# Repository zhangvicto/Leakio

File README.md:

## Inspiration
Over one-fourth of Canadians during their lifetimes will have to deal with water damage in their homes. This is an issue that causes many Canadians overwhelming stress from the sheer economical and residential implications. 

As an effort to assist and solve these very core issues, we have designed a solution that will allow for future leaks to be avoidable. Our prototype system made, composed of software and hardware will ensure house leaks are a thing of the past!

## What is our planned solution?

To prevent leaks, we have designed a system of components that when functioning together, would allow the user to monitor the status of their plumbing systems. 

Our system is comprised of:
> 
Two types of leak detection hardware
- Acoustic leak detectors: monitors abnormal sounds of pipes.
- Water detection probes: monitors the presence of water in unwanted areas.

Our hardware components will have the ability to send data to a local network, to then be stored in the cloud.

> Software components
- Secure cloud to store vital information regarding pipe leakages.
- Future planned app/website with the ability to receive such information

## Business Aspect of Leakio
Standalone, this solution is profitable through the aspect of selling the specific hardware to consumers. Although for insurance companies, this is a vital solution that has the potential to save millions of dollars.

It is far more economical to prevent a leak, rather than fix it when it already happens. The time of paying the average cost of $10,900 US dollars to fix water damage or a freezing claim is now avoidable!

In addition to saved funds, our planned system will be able to send information to insurance companies for specific data purposes such as which houses or areas have the most leaks, or individual risk assessment. This would allow insurance companies to more appropriately create better rates for the consumer, for the benefit of both consumer and insurance company.

## Software
### Front End:
This includes our app design in Figma, which was crafted using knowledge on proper design and ratios. Specifically, we wanted to create an app design that looked simple but had all the complex features that would seem professional. This is something we are proud of, as we feel this component was successful.

### Back End:
- PHP: website to retrieve data from Cloud SQL
- MySQL: access database through Raspberry Pi
- Python: using mysql connector to upload data to Cloud SQL
- Cloud SQL: Google MySQL database

## Hardware
### Electrical
- A custom PCB is designed from scratch using EAGLE
- Consists of USBC charging port, lithium battery charging circuit, ESP32, Water sensor connector, microphone connector
- The water sensor and microphone are extended from the PCB which is why they need a connector

### Custom Water Sensor
Two wires and an analog input.

### 3D-model
- Hub contains all the electronics and the sensors
- Easy to install design and places the microphone within the walls close to the pipes

## Challenges we ran into
### Front-End:
There were many challenges we ran into, especially regarding some technical aspects of Figma. Although the most challenging aspect in this would’ve been the implementation of the design.

### Back-End:
This is where most challenges were faced, which includes the making of the acoustic leak detector, proper sound recognition, cloud development, and data transfer.

It was our first time using MySQL, and learning how to use Google Cloud SQL. We also had to use both Python and PHP to retrieve and send data, two languages we are not super familiar with. 

We also had no idea how to set up a neural network with PyTorch. Also finding the proper data that can be used to train has proven to be very difficult. 

## Accomplishments that we're proud of
- Learning a lot of new things within a fast period of time. 
- Creating functional proof-of-concepts

## What we learned
Google Cloud: 
Creating a MySQL database and setting up a Deep Learning VM.

### MySQL:
Using MySQL and syntaxes, learning PHP.

### Machine Learning:
How to set up Pytorch.

### PCB Design:
Learning how to use EAGLE to design PCBs.

### Raspberry Pi:
Autorun Python scripts and splitting .wav files.

### Others:
Not to leave the recording to the last hour. It is hard to cut to 3 minutes with an explanation and demo. 

## What's next for Leakio
- Properly implement audio classification with Pytorth torchaudio
- Create possibly a network of devices in a single home
- Find more economical components
- Test on an ESP32

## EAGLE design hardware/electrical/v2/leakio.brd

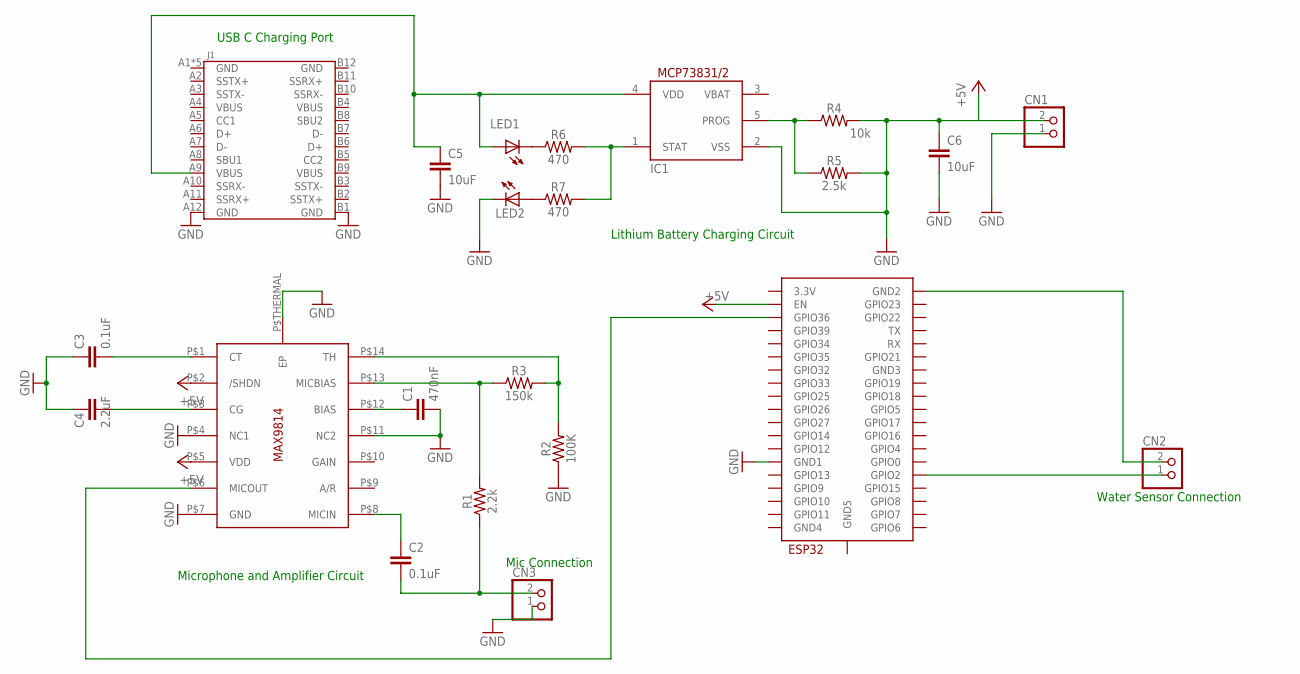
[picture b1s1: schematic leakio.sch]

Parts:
C1: 470nF; 0402
C2, C3: 0.1uF; 0402
C4: 2.2uF; 0603
C5, C6: 10uF; 0603
CN1: JST_2PIN-SMT-RA; JST-PH-2-SMT-RA
CN2, CN3: JST_2PIN-SMT; JST-PH-2-SMT
IC1: MCP73831/OT; SOT23-5L
J1: USBC-PTH; USB-C-PTH
LED1, LED2: LED; SMARTLED-TTW
R1: 2.2k; 0603
R2: 100K; 0402
R3: 150k; 0603
R4: 10k; 0603
R5: 2.5k; 0603
R6, R7: 470; 0603
U$1: ESP32-WROOM
U$2: MAX9814TDFN14; TDFN14_3X3MM

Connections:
+5V: C6.1, CN1.2 (1), IC1.2 (VSS), R4.2, R5.2, U$1.EN, U$2.P$2 (/SHDN), U$2.P$5 (VDD)
GND: C1.2, C3.1, C4.1, C5.2, C6.2, CN3.1 (2), J1.A12 (GND), J1.B1 (GND), LED2.C@1 (C), R2.1, U$1.GND1, U$2.P$4 (NC1), U$2.P$7 (GND), U$2.P$11 (NC2), U$2.P$THERMAL (EP)
unnamed: C3.2, U$2.P$1 (CT)
unnamed: C4.2, U$2.P$3 (CG)
unnamed: C5.1, IC1.4 (VDD), J1.A9 (VBUS), LED1.A@1 (A)
unnamed: U$1.SENSOR_VP (GPIO36), U$2.P$6 (MICOUT)
unnamed: C2.1, U$2.P$8 (MICIN)
unnamed: C2.2, CN3.2 (1), R1.1
unnamed: C1.1, U$2.P$12 (BIAS)
unnamed: LED2.A@1 (A), R7.1
unnamed: R1.2, R3.1, U$2.P$13 (MICBIAS)
unnamed: R2.2, R3.2, U$2.P$14 (TH)
unnamed: IC1.5 (PROG), R4.1, R5.1
unnamed: LED1.C@1 (C), R6.1
unnamed: CN2.1 (2), U$1.IO2 (GPIO2)
unnamed: CN2.2 (1), U$1.GND2
unnamed: IC1.1 (STAT), R6.2, R7.2

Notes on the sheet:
Water Sensor Connection
Microphone and Amplifier Circuit
USB C Charging Port
Lithium Battery Charging Circuit
Mic Connection

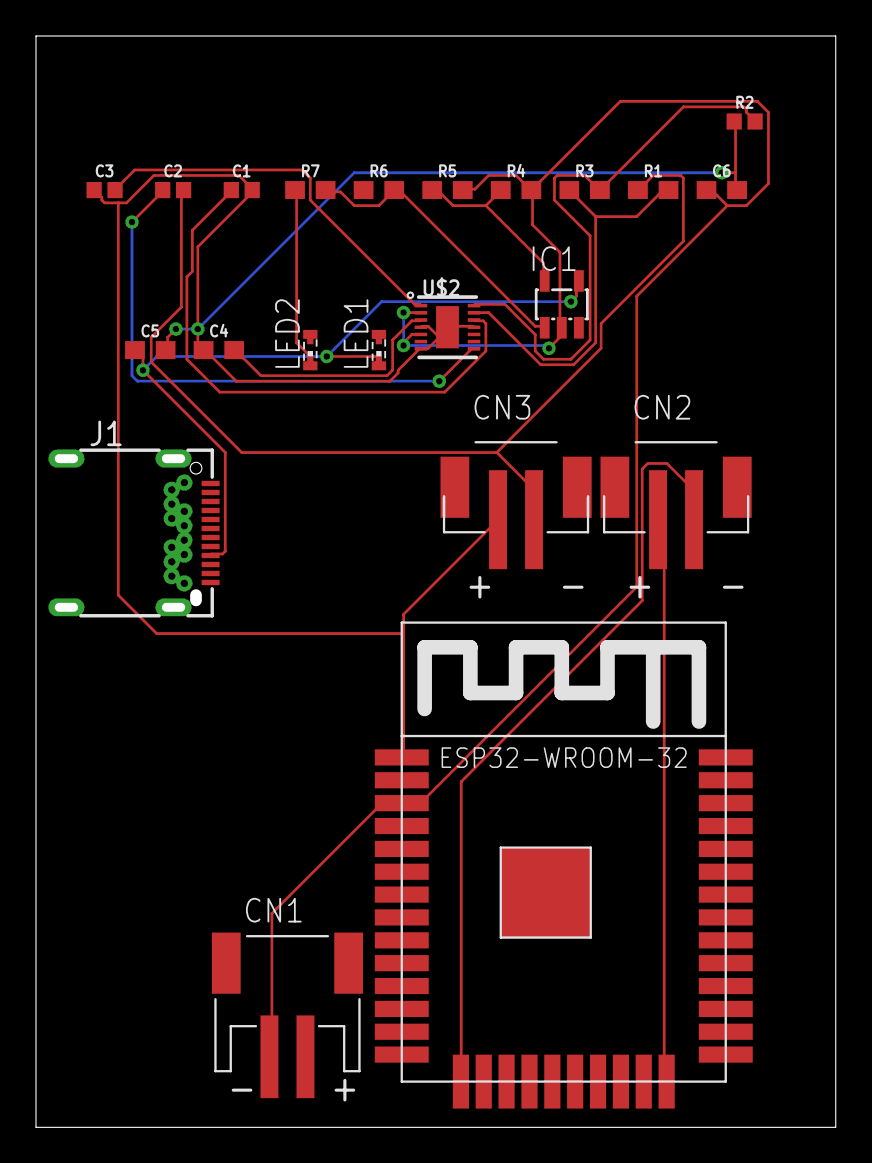
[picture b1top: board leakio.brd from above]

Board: 2 copper layers, 43.8 x 60.0 mm, 22 parts (0 on the bottom side), 17 nets.

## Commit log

2021-08-21 ESP32 pins
2021-08-21 name change
2021-08-21 tested sql
2021-08-21 fix sql line 2
2021-08-21 sql fix x3
2021-08-21 Create CNAME
2021-08-21 dataset split
2021-08-21 Finally uploaded file to database
2021-08-21 Update CNAME
2021-08-22 website update
2021-08-22 website frame complete
2021-08-22 update with php
2021-08-22 upload 3d model files
2021-08-22 pcb upload
2021-08-22 images and render
2021-08-22 finally fixed php retrieving data
2021-08-22 last update
2021-08-23 update github description
2021-08-23 fix readme
2021-08-23 readme update

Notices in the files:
parts and their libraries:
SparkFun-Capacitors: Licensing: Creative Commons ShareAlike 4.0 International - https://creativecommons.org/licenses/by-sa/4.0
